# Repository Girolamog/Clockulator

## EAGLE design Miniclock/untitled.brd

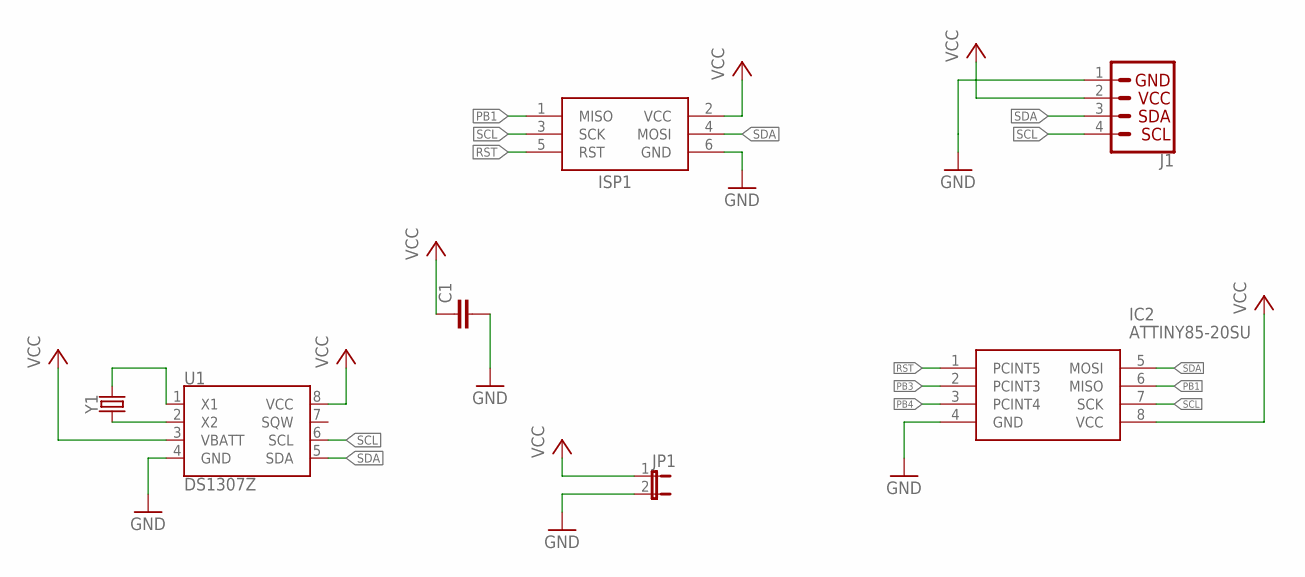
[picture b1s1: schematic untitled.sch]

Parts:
C1: C-EUC1206; C1206
IC2: ATTINY85-20SU; SOT127P798X216-8N
ISP1: AVRISP-6; AVRISP
J1: I2C_STANDARD; 1X04
JP1: JUMPER-2-OLDPTH; 1X02
U1: DS1307Z; SO08-0.15
Y1: CRYSTALPTH-2X6; CRYSTAL-PTH-2X6-CYL

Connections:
GND: C1.2, IC2.4 (GND), ISP1.6 (GND), J1.1, JP1.2, U1.4 (GND)
unnamed: U1.2 (X2), Y1.1
unnamed: U1.1 (X1), Y1.2
PB1: IC2.6 (MISO), ISP1.1 (MISO)
PB3: IC2.2 (PCINT3)
PB4: IC2.3 (PCINT4)
RST: IC2.1 (PCINT5), ISP1.5 (RST)
SCL: IC2.7 (SCK), ISP1.3 (SCK), J1.4, U1.6 (SCL)
SDA: IC2.5 (MOSI), ISP1.4 (MOSI), J1.3, U1.5 (SDA)
VCC: C1.1, IC2.8 (VCC), ISP1.2 (VCC), J1.2, JP1.1, U1.3 (VBATT), U1.8 (VCC)

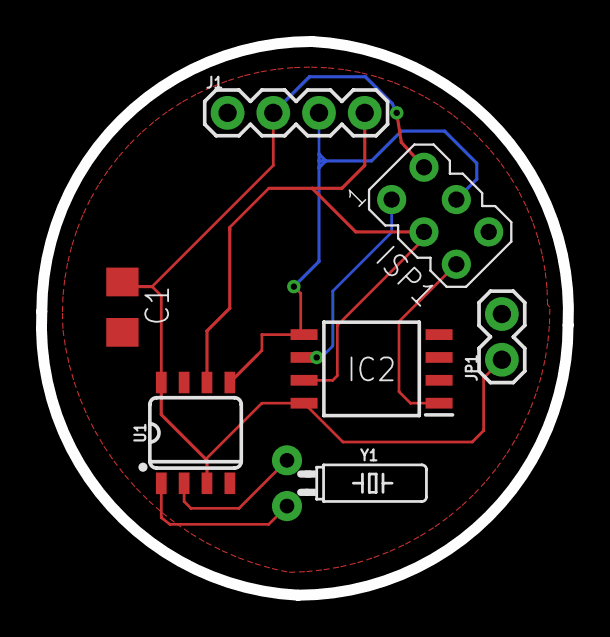
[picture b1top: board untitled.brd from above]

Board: 2 copper layers, 29.3 x 30.8 mm, 8 parts (1 on the bottom side), 8 nets.

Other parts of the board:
U$1: OSHW-LOGO-M

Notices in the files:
parts and their libraries:
SparkFun-Connectors: Licensing: Creative Commons ShareAlike 4.0 International - https://creativecommons.org/licenses/by-sa/4.0
